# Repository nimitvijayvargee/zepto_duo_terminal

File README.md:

# zepto_duo_terminal
An old school-style VGA output terminal PC!
The PC is powered by two Raspberry Pi Picos. One of the Pico handles the main processing and the keyboard matrix (CPU Pico) and the other Pico handles the VGA Output and the conversion between text to pixels (GPU Pico). The Picos can be replaced with any Pin-compatible version.

## VGA DAC
The GPU Pico is connected to a Resistor DAC that outputs VGA compatible voltage values. There are 5 bits of resolution for each colour channel (RGB555), which allows for 32K colours. The values for the DAC are as 500, 1K, 2K, and 5.1K (commonly used values).

## Keyboard Matrix 
The Keyboard matrix is composed of 8 Rows and 8 Columns, following an ortholinear keyboard layout. Sticky (toggle) keys is also enabled by default to make using the keyboard easier. The keyboard features a "Special" key instead of the commly used Fn or GUI keys. The keycaps are all custom becuase of their specific use case and the unorthodox ortholinear layout.

# Pictures

# BOM
|Item                  |Cost|
|----------------------|----|
|DB-15 VGA Connector   |[1](https://roboticsdna.in/product/db15-female-pcb-mount-right-angle-connector-2-pcs/)   |
|1N4148 Diodes         |[5](https://roboticsdna.in/product/diode-1n4148/)   |
|LEDs                  |[0.5](https://roboticsdna.in/product/super-bright-white-led-3mm-1000-pcs/) |
|Raspberry Pi Pico (x2)|[10](https://roboticsdna.in/product/raspberry-pi-pico/)  |
|Headers               |[0.5](https://roboticsdna.in/product/40x1-10mm-2-5mm-pitch-burg-strip-male-straight-brass-high-quality-pack-of-5/) |
|PCB (400x120mm)       |[75](https://www.pcbpower.com/page/pcb-fabrication)  |
|Case + Keycaps        |    |
|Switches              |[20](https://stackskb.com/store/akko-v3-cream-blue-pro-switch-pack-of-45/)  |
|Solder                |[5](https://roboticsdna.in/product/dl-premium-solder-wire-63-37-22-swg-50gm/)  |
|TOTAL                 |117 |

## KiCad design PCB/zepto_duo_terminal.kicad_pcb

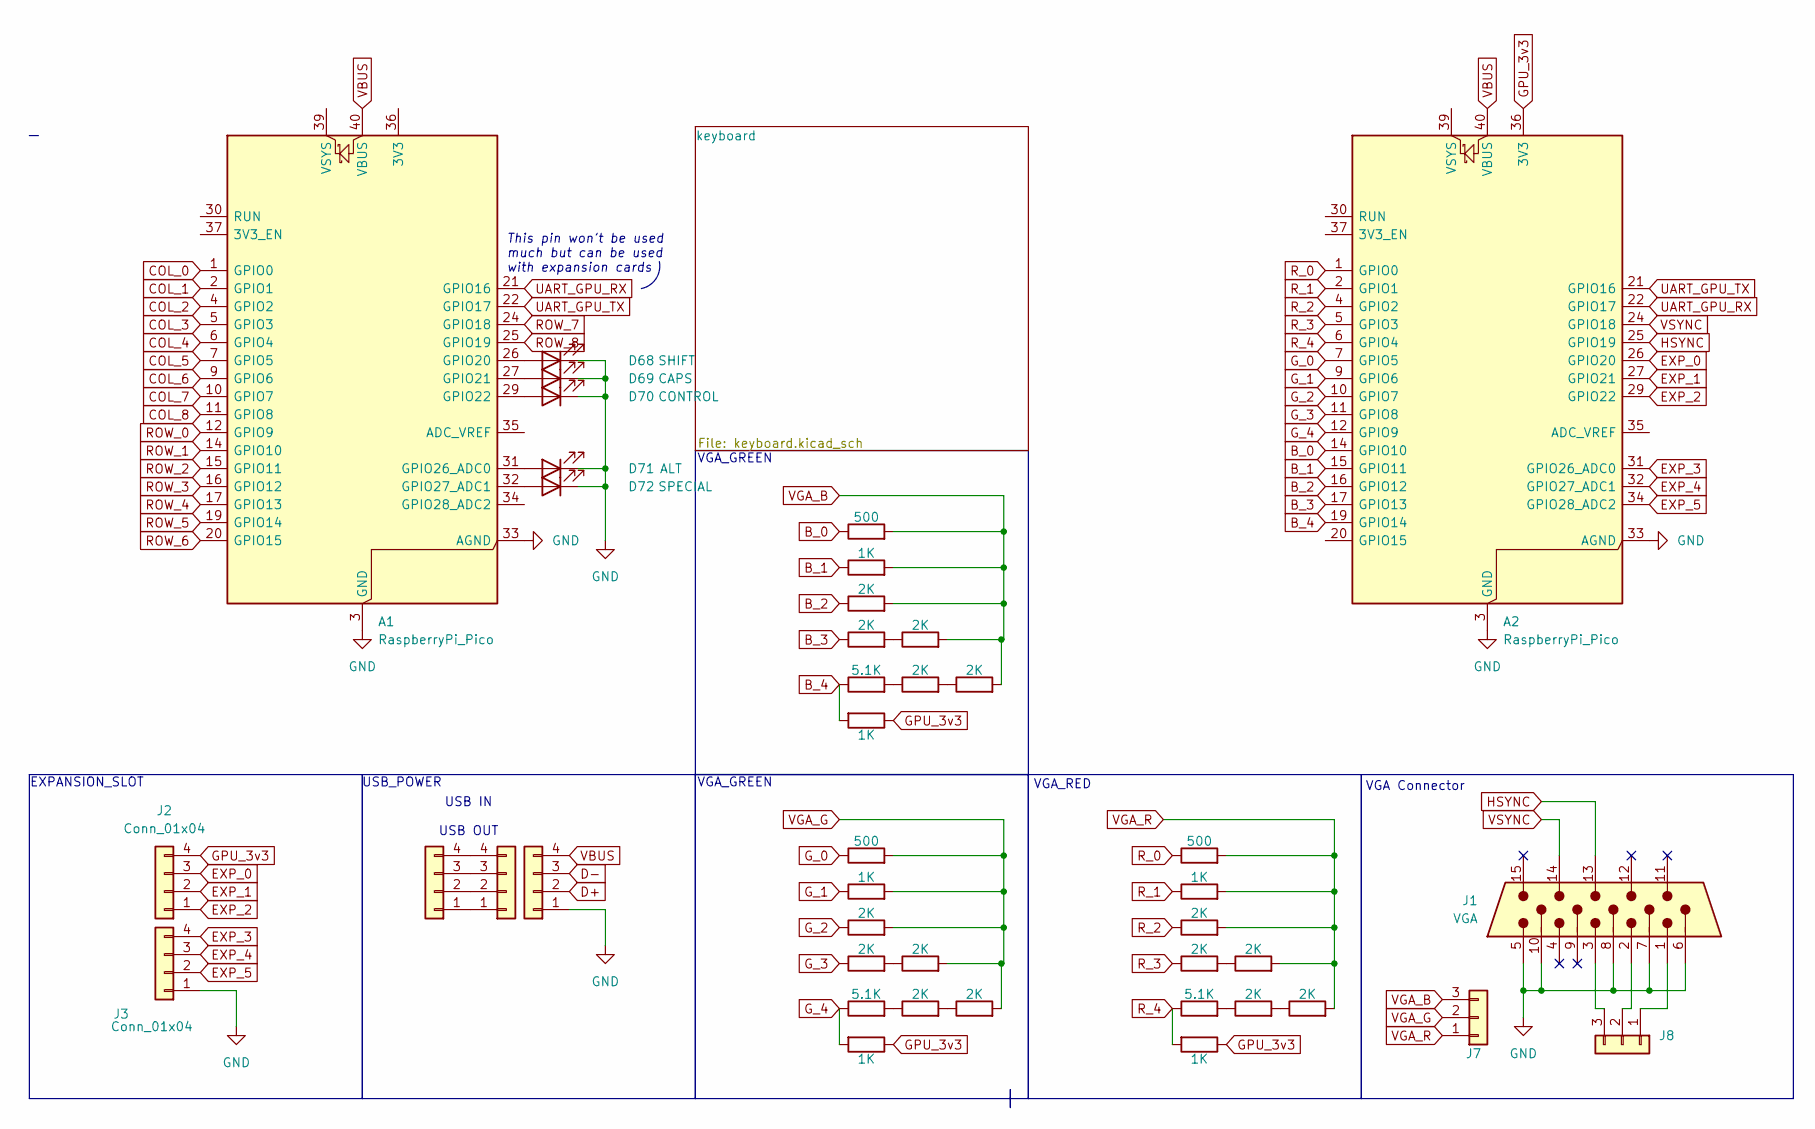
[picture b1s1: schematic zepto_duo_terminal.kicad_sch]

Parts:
A1, A2: RaspberryPi_Pico; RaspberryPi_Pico_Common_THT
D68: SHIFT; LED_D3.0mm
D69: CAPS; LED_D3.0mm
D70: CONTROL; LED_D3.0mm
D71: ALT; LED_D3.0mm
D72: SPECIAL; LED_D3.0mm
J1: VGA; DSUB-15-HD_Pins_Horizontal_P2.29x1.90mm_EdgePinOffset3.03mm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
J2, J3, J4, J5, J6: Conn_01x04; PinHeader_1x04_P2.54mm_Vertical
J7, J8: Conn_01x03; PinHeader_1x03_P2.54mm_Vertical
R1, R10, R19: 500; D_DO-35_SOD27_P7.62mm_Horizontal
R2, R9, R11, R15, R20, R24: 1K; D_DO-35_SOD27_P7.62mm_Horizontal
R3, R4, R5, R7, R8, R12, R13, R16, R17, R18, R21, R22, R25, R26, R27: 2K; D_DO-35_SOD27_P7.62mm_Horizontal
R6, R14, R23: 5.1K; D_DO-35_SOD27_P7.62mm_Horizontal

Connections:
B_0: A2.14 (GPIO10), R19.1
B_1: A2.15 (GPIO11), R20.1
B_2: A2.16 (GPIO12), R21.1
B_3: A2.17 (GPIO13), R22.1
B_4: A2.19 (GPIO14), R23.1, R24.2
COL_0: A1.1 (GPIO0); also elsewhere on the board
COL_1: A1.2 (GPIO1); also elsewhere on the board
COL_2: A1.4 (GPIO2); also elsewhere on the board
COL_3: A1.5 (GPIO3); also elsewhere on the board
COL_4: A1.6 (GPIO4); also elsewhere on the board
COL_5: A1.7 (GPIO5); also elsewhere on the board
COL_6: A1.9 (GPIO6); also elsewhere on the board
COL_7: A1.10 (GPIO7); also elsewhere on the board
COL_8: A1.11 (GPIO8); also elsewhere on the board
D+: J5.2
D-: J5.3
EXP_0: A2.26 (GPIO20), J2.3
EXP_1: A2.27 (GPIO21), J2.2
EXP_2: A2.29 (GPIO22), J2.1
EXP_3: A2.31 (GPIO26_ADC0), J3.4
EXP_4: A2.32 (GPIO27_ADC1), J3.3
EXP_5: A2.34 (GPIO28_ADC2), J3.2
GND: A1.3 (GND), A1.8 (GND), A1.13 (GND), A1.18 (GND), A1.23 (GND), A1.28 (GND), A1.33 (AGND), A1.38 (GND), A2.3 (GND), A2.8 (GND), A2.13 (GND), A2.18 (GND), A2.23 (GND), A2.28 (GND), A2.33 (AGND), A2.38 (GND), D68.1 (K), D69.1 (K), D70.1 (K), D71.1 (K), D72.1 (K), J1.5, J1.6, J1.7, J1.8, J1.10, J3.1, J5.1
GPU_3v3: A2.36 (3V3), J2.4, R9.1, R15.1, R24.1
G_0: A2.7 (GPIO5), R10.1
G_1: A2.9 (GPIO6), R11.1
G_2: A2.10 (GPIO7), R12.1
G_3: A2.11 (GPIO8), R13.1
G_4: A2.12 (GPIO9), R14.1, R15.2
HSYNC: A2.25 (GPIO19), J1.13
unnamed: A1.26 (GPIO20), D68.2 (A)
unnamed: A1.27 (GPIO21), D69.2 (A)
unnamed: A1.29 (GPIO22), D70.2 (A)
unnamed: A1.31 (GPIO26_ADC0), D71.2 (A)
unnamed: A1.32 (GPIO27_ADC1), D72.2 (A)
unnamed: J4.1, J6.1
unnamed: J4.2, J6.2
unnamed: J4.3, J6.3
unnamed: J4.4, J6.4
unnamed: J1.1, J8.1
unnamed: J1.2, J8.2
unnamed: J1.3, J8.3
unnamed: R4.2, R5.1
unnamed: R6.2, R7.1
unnamed: R7.2, R8.1
unnamed: R13.2, R16.1
unnamed: R14.2, R17.1
unnamed: R17.2, R18.1
unnamed: R22.2, R25.1
unnamed: R23.2, R26.1
unnamed: R26.2, R27.1
ROW_0: A1.12 (GPIO9); also elsewhere on the board
ROW_1: A1.14 (GPIO10); also elsewhere on the board
ROW_2: A1.15 (GPIO11); also elsewhere on the board
ROW_3: A1.16 (GPIO12); also elsewhere on the board
ROW_4: A1.17 (GPIO13); also elsewhere on the board
ROW_5: A1.19 (GPIO14); also elsewhere on the board
ROW_6: A1.20 (GPIO15); also elsewhere on the board
ROW_7: A1.24 (GPIO18); also elsewhere on the board
ROW_8: A1.25 (GPIO19); also elsewhere on the board
R_0: A2.1 (GPIO0), R1.1
R_1: A2.2 (GPIO1), R2.1
R_2: A2.4 (GPIO2), R3.1
R_3: A2.5 (GPIO3), R4.1
R_4: A2.6 (GPIO4), R6.1, R9.2
UART_GPU_RX: A1.21 (GPIO16), A2.22 (GPIO17)
UART_GPU_TX: A1.22 (GPIO17), A2.21 (GPIO16)
VBUS: A1.40 (VBUS), A2.40 (VBUS), J5.4
VGA_B: J7.3, R19.2, R20.2, R21.2, R25.2, R27.2
VGA_G: J7.2, R10.2, R11.2, R12.2, R16.2, R18.2
VGA_R: J7.1, R1.2, R2.2, R3.2, R5.2, R8.2
VSYNC: A2.24 (GPIO18), J1.14

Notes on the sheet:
VGA Connector
USB_POWER
USB IN USB OUT
VGA_RED
This pin won't be used much but can be used with expansion cards
EXPANSION_SLOT
VGA_GREEN

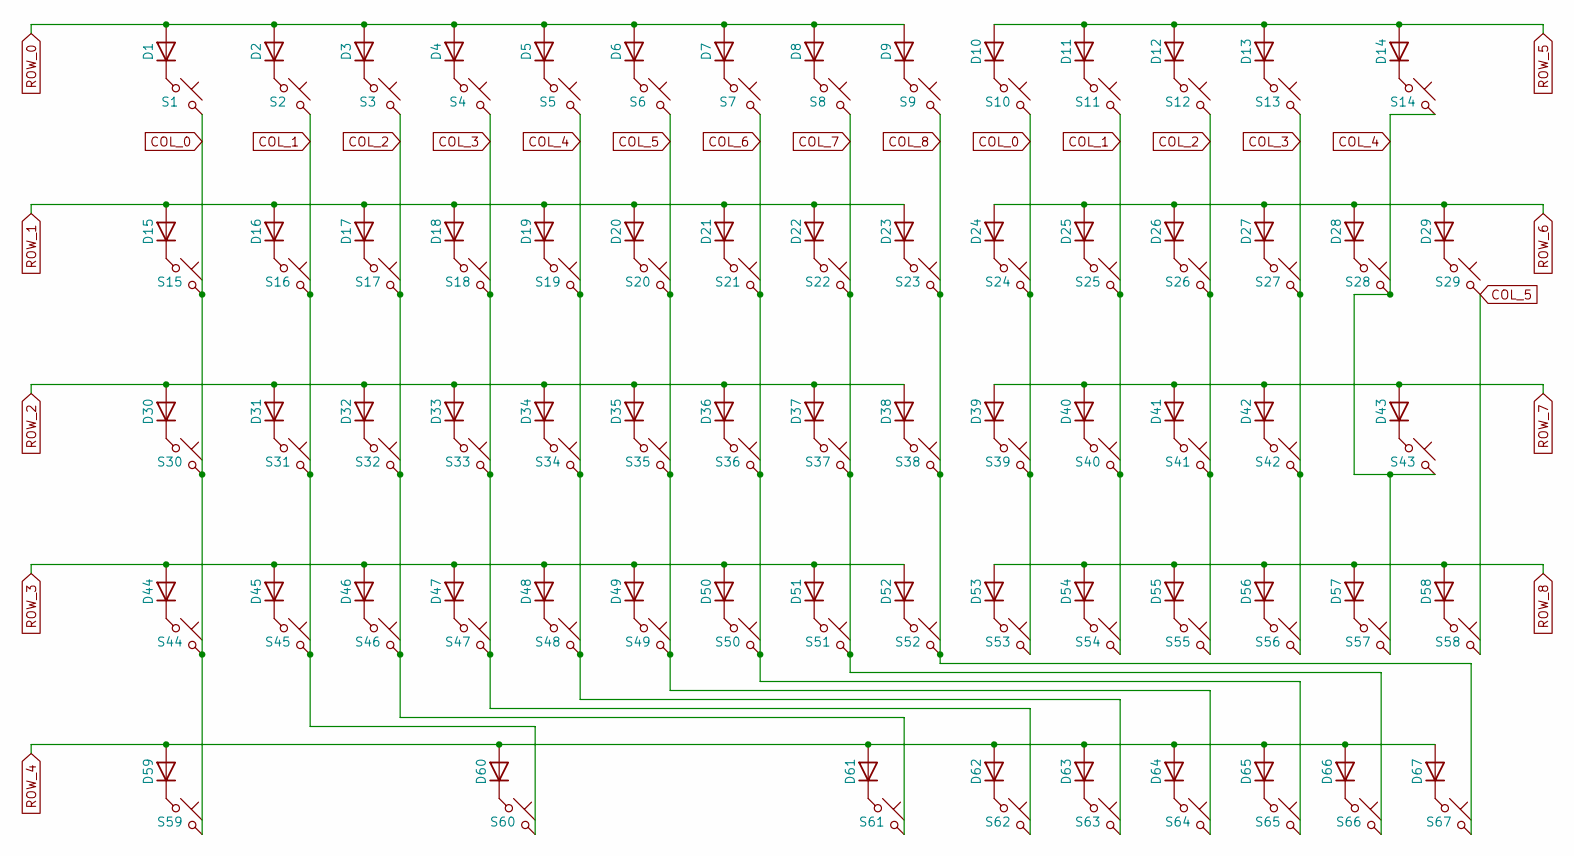
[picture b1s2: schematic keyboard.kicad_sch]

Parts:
D1, D2, D3, D4, D5, D6, D7, D8, D9, D10, D11, D12, D13, D14, D15, D16, D17, D18, D19, D20, D21, D22, D23, D24, D25, D26, D27, D28, D29, D30, D31, D32, D33, D34, D35, D36, D37, D38, D39, D40, D41, D42, D43, D44, D45, D46, D47, D48, D49, D50, D51, D52, D53, D54, D55, D56, D57, D58, D59, D60, D61, D62, D63, D64, D65, D66, D67: Diode; D_DO-35_SOD27_P7.62mm_Horizontal
S1, S15, S30, S44, S59: Keyswitch; MX_PCB_1.50u
S2, S3, S4, S5, S6, S7, S8, S9, S10, S11, S12, S13, S16, S17, S18, S19, S20, S21, S22, S23, S24, S25, S26, S27, S28, S29, S31, S32, S33, S34, S35, S36, S37, S38, S39, S40, S41, S42, S45, S46, S47, S48, S49, S50, S51, S52, S53, S54, S55, S56, S57, S58, S62, S63, S64, S65, S66, S67: Keyswitch; MX_PCB_1.00u
S14, S43: Keyswitch; MX_PCB_2.00u
S60: Keyswitch; MX_PCB_6.25u
S61: Keyswitch; MX_PCB_1.25u

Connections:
COL_0: S1.2, S10.2, S15.2, S24.2, S30.2, S39.2, S44.2, S53.2, S59.2; also elsewhere on the board
COL_1: S2.2, S11.2, S16.2, S25.2, S31.2, S40.2, S45.2, S54.2, S60.2; also elsewhere on the board
COL_2: S3.2, S12.2, S17.2, S26.2, S32.2, S41.2, S46.2, S55.2, S61.2; also elsewhere on the board
COL_3: S4.2, S13.2, S18.2, S27.2, S33.2, S42.2, S47.2, S56.2, S62.2; also elsewhere on the board
COL_4: S5.2, S14.2, S19.2, S28.2, S34.2, S43.2, S48.2, S57.2, S63.2; also elsewhere on the board
COL_5: S6.2, S20.2, S29.2, S35.2, S49.2, S58.2, S64.2; also elsewhere on the board
COL_6: S7.2, S21.2, S36.2, S50.2, S65.2; also elsewhere on the board
COL_7: S8.2, S22.2, S37.2, S51.2, S66.2; also elsewhere on the board
COL_8: S9.2, S23.2, S38.2, S52.2, S67.2; also elsewhere on the board
unnamed: D1.1 (K), S1.1
unnamed: D2.1 (K), S2.1
unnamed: D3.1 (K), S3.1
unnamed: D4.1 (K), S4.1
unnamed: D5.1 (K), S5.1
unnamed: D6.1 (K), S6.1
unnamed: D7.1 (K), S7.1
unnamed: D8.1 (K), S8.1
unnamed: D9.1 (K), S9.1
unnamed: D10.1 (K), S10.1
unnamed: D11.1 (K), S11.1
unnamed: D12.1 (K), S12.1
unnamed: D13.1 (K), S13.1
unnamed: D14.1 (K), S14.1
unnamed: D15.1 (K), S15.1
unnamed: D16.1 (K), S16.1
unnamed: D17.1 (K), S17.1
unnamed: D18.1 (K), S18.1
unnamed: D19.1 (K), S19.1
unnamed: D20.1 (K), S20.1
unnamed: D21.1 (K), S21.1
unnamed: D22.1 (K), S22.1
unnamed: D23.1 (K), S23.1
unnamed: D24.1 (K), S24.1
unnamed: D25.1 (K), S25.1
unnamed: D26.1 (K), S26.1
unnamed: D27.1 (K), S27.1
unnamed: D28.1 (K), S28.1
unnamed: D29.1 (K), S29.1
unnamed: D30.1 (K), S30.1
unnamed: D31.1 (K), S31.1
unnamed: D32.1 (K), S32.1
unnamed: D33.1 (K), S33.1
unnamed: D34.1 (K), S34.1
unnamed: D35.1 (K), S35.1
unnamed: D36.1 (K), S36.1
unnamed: D37.1 (K), S37.1
unnamed: D38.1 (K), S38.1
unnamed: D39.1 (K), S39.1
unnamed: D40.1 (K), S40.1
unnamed: D41.1 (K), S41.1
unnamed: D42.1 (K), S42.1
unnamed: D43.1 (K), S43.1
unnamed: D44.1 (K), S44.1
unnamed: D45.1 (K), S45.1
unnamed: D46.1 (K), S46.1
unnamed: D47.1 (K), S47.1
unnamed: D48.1 (K), S48.1
unnamed: D49.1 (K), S49.1
unnamed: D50.1 (K), S50.1
unnamed: D51.1 (K), S51.1
unnamed: D52.1 (K), S52.1
unnamed: D53.1 (K), S53.1
unnamed: D54.1 (K), S54.1
unnamed: D55.1 (K), S55.1
unnamed: D56.1 (K), S56.1
unnamed: D57.1 (K), S57.1
unnamed: D58.1 (K), S58.1
unnamed: D59.1 (K), S59.1
unnamed: D60.1 (K), S60.1
unnamed: D61.1 (K), S61.1
unnamed: D62.1 (K), S62.1
unnamed: D63.1 (K), S63.1
unnamed: D64.1 (K), S64.1
unnamed: D65.1 (K), S65.1
unnamed: D66.1 (K), S66.1
unnamed: D67.1 (K), S67.1
ROW_0: D1.2 (A), D2.2 (A), D3.2 (A), D4.2 (A), D5.2 (A), D6.2 (A), D7.2 (A), D8.2 (A), D9.2 (A); also elsewhere on the board
ROW_1: D15.2 (A), D16.2 (A), D17.2 (A), D18.2 (A), D19.2 (A), D20.2 (A), D21.2 (A), D22.2 (A), D23.2 (A); also elsewhere on the board
ROW_2: D30.2 (A), D31.2 (A), D32.2 (A), D33.2 (A), D34.2 (A), D35.2 (A), D36.2 (A), D37.2 (A), D38.2 (A); also elsewhere on the board
ROW_3: D44.2 (A), D45.2 (A), D46.2 (A), D47.2 (A), D48.2 (A), D49.2 (A), D50.2 (A), D51.2 (A), D52.2 (A); also elsewhere on the board
ROW_4: D59.2 (A), D60.2 (A), D61.2 (A), D62.2 (A), D63.2 (A), D64.2 (A), D65.2 (A), D66.2 (A), D67.2 (A); also elsewhere on the board
ROW_5: D10.2 (A), D11.2 (A), D12.2 (A), D13.2 (A), D14.2 (A); also elsewhere on the board
ROW_6: D24.2 (A), D25.2 (A), D26.2 (A), D27.2 (A), D28.2 (A), D29.2 (A); also elsewhere on the board
ROW_7: D39.2 (A), D40.2 (A), D41.2 (A), D42.2 (A), D43.2 (A); also elsewhere on the board
ROW_8: D53.2 (A), D54.2 (A), D55.2 (A), D56.2 (A), D57.2 (A), D58.2 (A); also elsewhere on the board

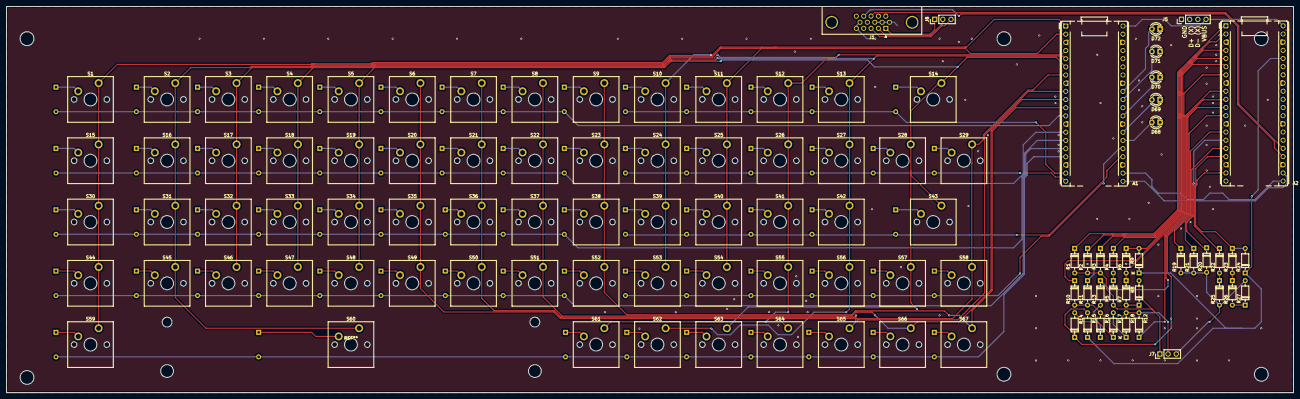
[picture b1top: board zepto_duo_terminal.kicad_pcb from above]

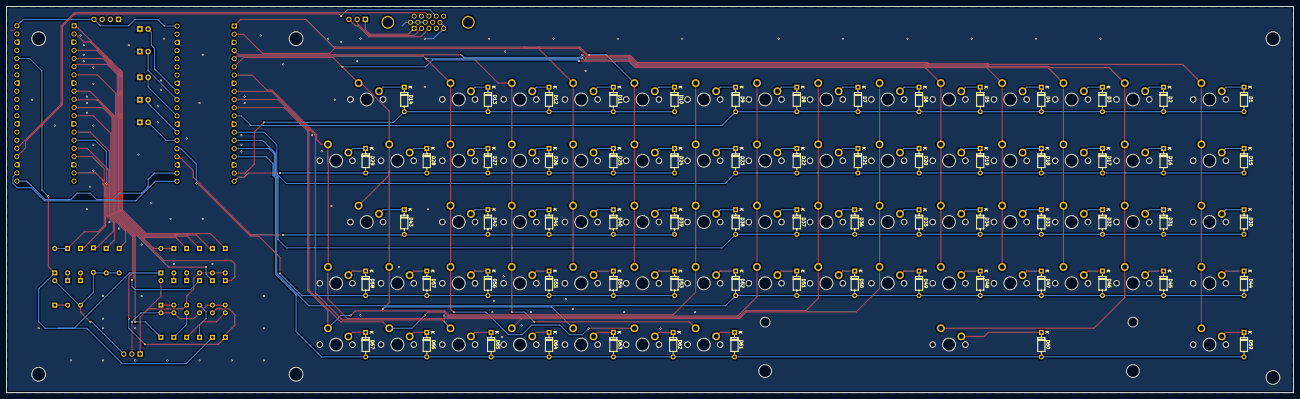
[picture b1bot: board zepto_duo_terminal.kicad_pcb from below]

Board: 2 copper layers, 400.0 x 120.0 mm, 172 parts (67 on the bottom side), 127 nets.

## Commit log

2025-07-14 stupid line break stupid line break stupid line break
2025-07-17 Complete README and CAD
2025-07-17 Rename image.png to image-0.png
2025-07-26 Rename code.py to code/CIRCUITPYTHON_GPU_TEST.py
2025-07-26 Rename keymap.py to code/CIRCUITPYTHON_CPU_KEYMAP_UART.py
2025-07-26 Rename image.png to image-5.png
2025-07-26 Rename image.png to image-6.png
2025-07-31 Fixed Gerbers
2025-08-14 Minor changes to case and PCB
